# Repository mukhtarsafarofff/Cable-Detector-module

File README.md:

(ENG) I have designed this circuit to detect cable problems.

(DEU) Ich habe diesen Schaltkreis entworfen, um Kabelprobleme zu erkennen.

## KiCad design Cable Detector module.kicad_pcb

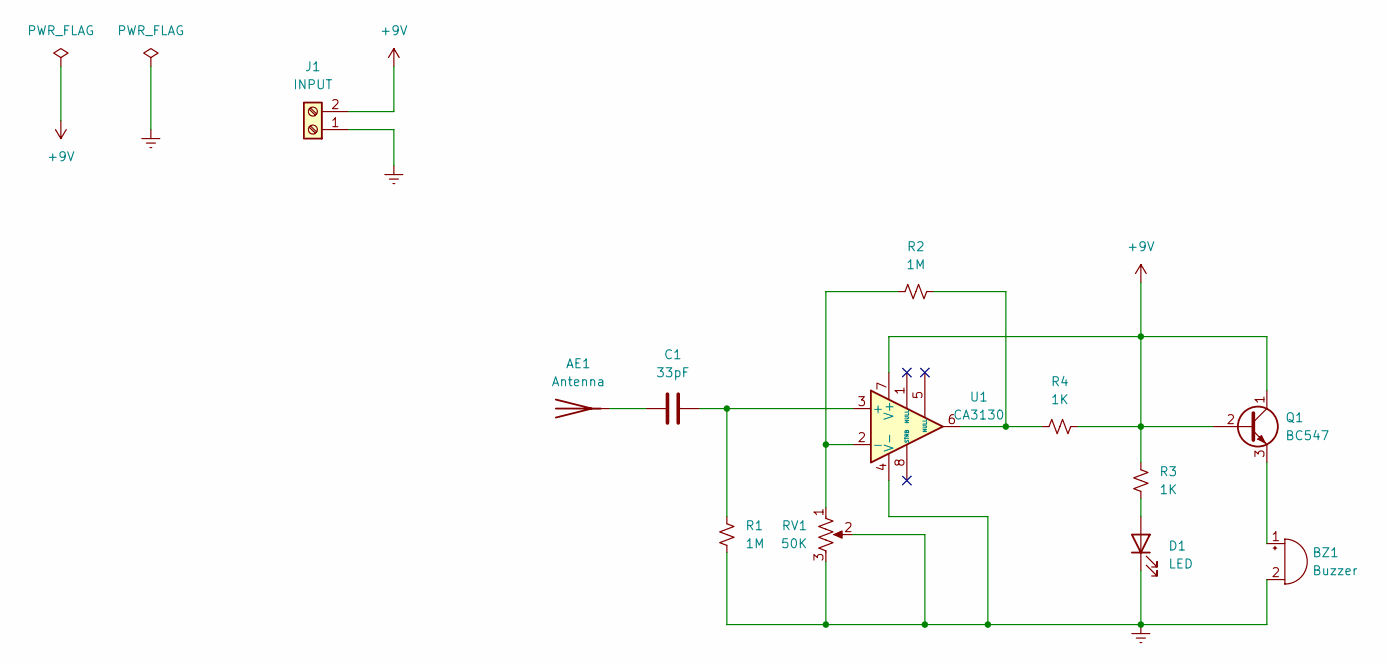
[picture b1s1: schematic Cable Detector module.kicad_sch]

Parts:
AE1: Antenna; TerminalBlock_MetzConnect_360271_1x01_Horizontal_ScrewM3.0_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
BZ1: Buzzer; Buzzer_15x7.5RM7.6
C1: 33pF; C_Disc_D7.5mm_W5.0mm_P7.50mm
D1: LED; LED_D5.0mm
J1: INPUT; TerminalBlock_bornier-2_P5.08mm
Q1: BC547; TO-92_Inline
R1, R2: 1M; R_Axial_DIN0309_L9.0mm_D3.2mm_P12.70mm_Horizontal
R3, R4: 1K; R_Axial_DIN0309_L9.0mm_D3.2mm_P12.70mm_Horizontal
RV1: 50K; Potentiometer_Vishay_148-149_Single_Horizontal
U1: CA3130; DIP-8_W7.62mm

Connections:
+9V: J1.2, Q1.1 (C), Q1.2 (B), R3.1, R4.2, U1.7 (V+)
Earth: BZ1.2 (+), D1.1 (K), J1.1, R1.2, RV1.2, RV1.3, U1.4 (V-)
unnamed: AE1.1 (A), C1.1
unnamed: BZ1.1 (-), Q1.3 (E)
unnamed: D1.2 (A), R3.2
unnamed: R2.2, R4.1, U1.6
unnamed: C1.2, R1.1, U1.3 (+)
unnamed: R2.1, RV1.1, U1.2 (-)

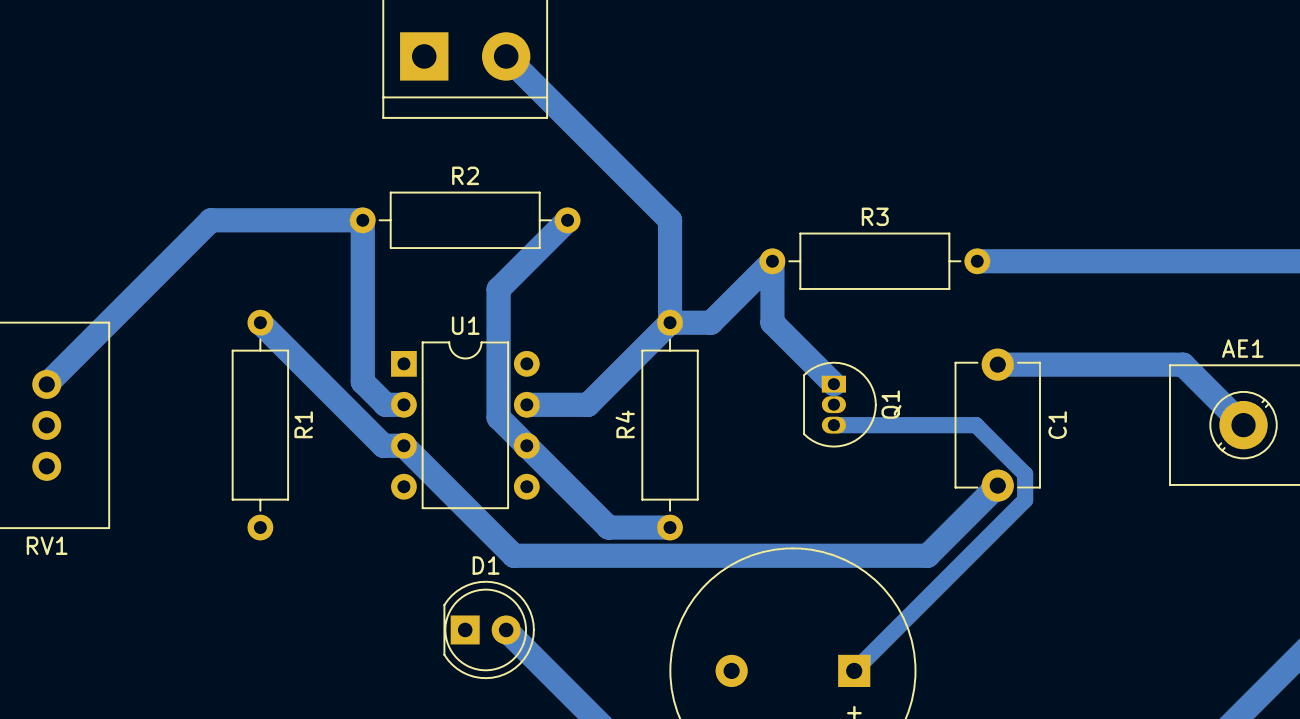
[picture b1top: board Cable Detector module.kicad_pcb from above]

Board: 2 copper layers, 12 parts (0 on the bottom side), 8 nets.

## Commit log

2024-03-18 Cable detector module is accomplished
2024-03-26 Cable Detector Module is renewed
